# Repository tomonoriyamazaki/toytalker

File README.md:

# ToyTalker

子供向け音声AIおもちゃ。話しかけると、好きなキャラクターの声で返事をしてくれる。

## 特徴

- **応答約2秒**: STT→LLM→TTSを全区間ストリーミングでつなぎ、最初の音声チャンクが生成され次第再生を開始。サーバーレス（AWS Lambda）構成のまま体感レイテンシを最小化
- **相槌**: メインの応答を生成している間に「そうだね〜」などの短い繋ぎ応答を先に返し、会話のテンポを保つ
- **ボイス・キャラクター切替**: TTSプロバイダーをプラガブルに切替可能（OpenAI / Google / Gemini / ElevenLabs / Cartesia / FishAudio / ずんだもん / 自前クローンボイス）。キャラクターの人格プロンプトもDBで管理
- **スタンドアロン動作**: ESP32-S3搭載の専用基板、おもちゃ単体でWiFi経由でAWSと直接通信（設定ではスマホが必要）

## しくみ
https://github.com/user-attachments/assets/177e0598-6c0a-4d14-9477-36d719003d13

```
[スマホアプリ / ESP32] ── 音声 ──> Soniox STT（直接WebSocket接続）
        │                              │ テキスト
        │                              v
        │<── 音声ストリーム ── Lambda（LLM → TTS ストリーミング）
        │<── 繋ぎ応答 ─────── Lambda（相槌）
```

- STTはLambdaを経由せず、一時キーを使ってクライアントからSonioxへ直接接続（ボトルネック回避）
- LLM→TTSは直列ストリーミングで、生成しながら順次音声化・再生

## デバイスの変遷

| 世代 | 構成 | 状態 |
|---|---|---|
| v1 | Raspberry Pi | 検証完了 |
| v2 | ブレッドボード | 検証完了 |
| v3 | ESP32-S3スタンドアロン（専用PCB） | 開発中 |

## 参加プログラム

- SS Bootcamp 3rd #2025
- TiB FAB makers challenge 2025
- SS Bootcamp 4th #2026

## ドキュメント

- [開発のあゆみ（初期からの検討・試行錯誤の記録）](docs/history.md)
- [マイコン（ESP32）実装](docs/mcu.md)
- [スマホアプリ実装](app/README.md)
- [自前クローンボイス（RTX 5090 / Qwen3-TTS）のバッチ推論](docs/qwen3-tts-batch-engine-2026-09-12.md)
- [原価と課金の考え方](docs/pricing-and-cost-model.md)
- [製品化の認証チェックリスト（STマーク・技適・PSE）](docs/certification-checklist.md)

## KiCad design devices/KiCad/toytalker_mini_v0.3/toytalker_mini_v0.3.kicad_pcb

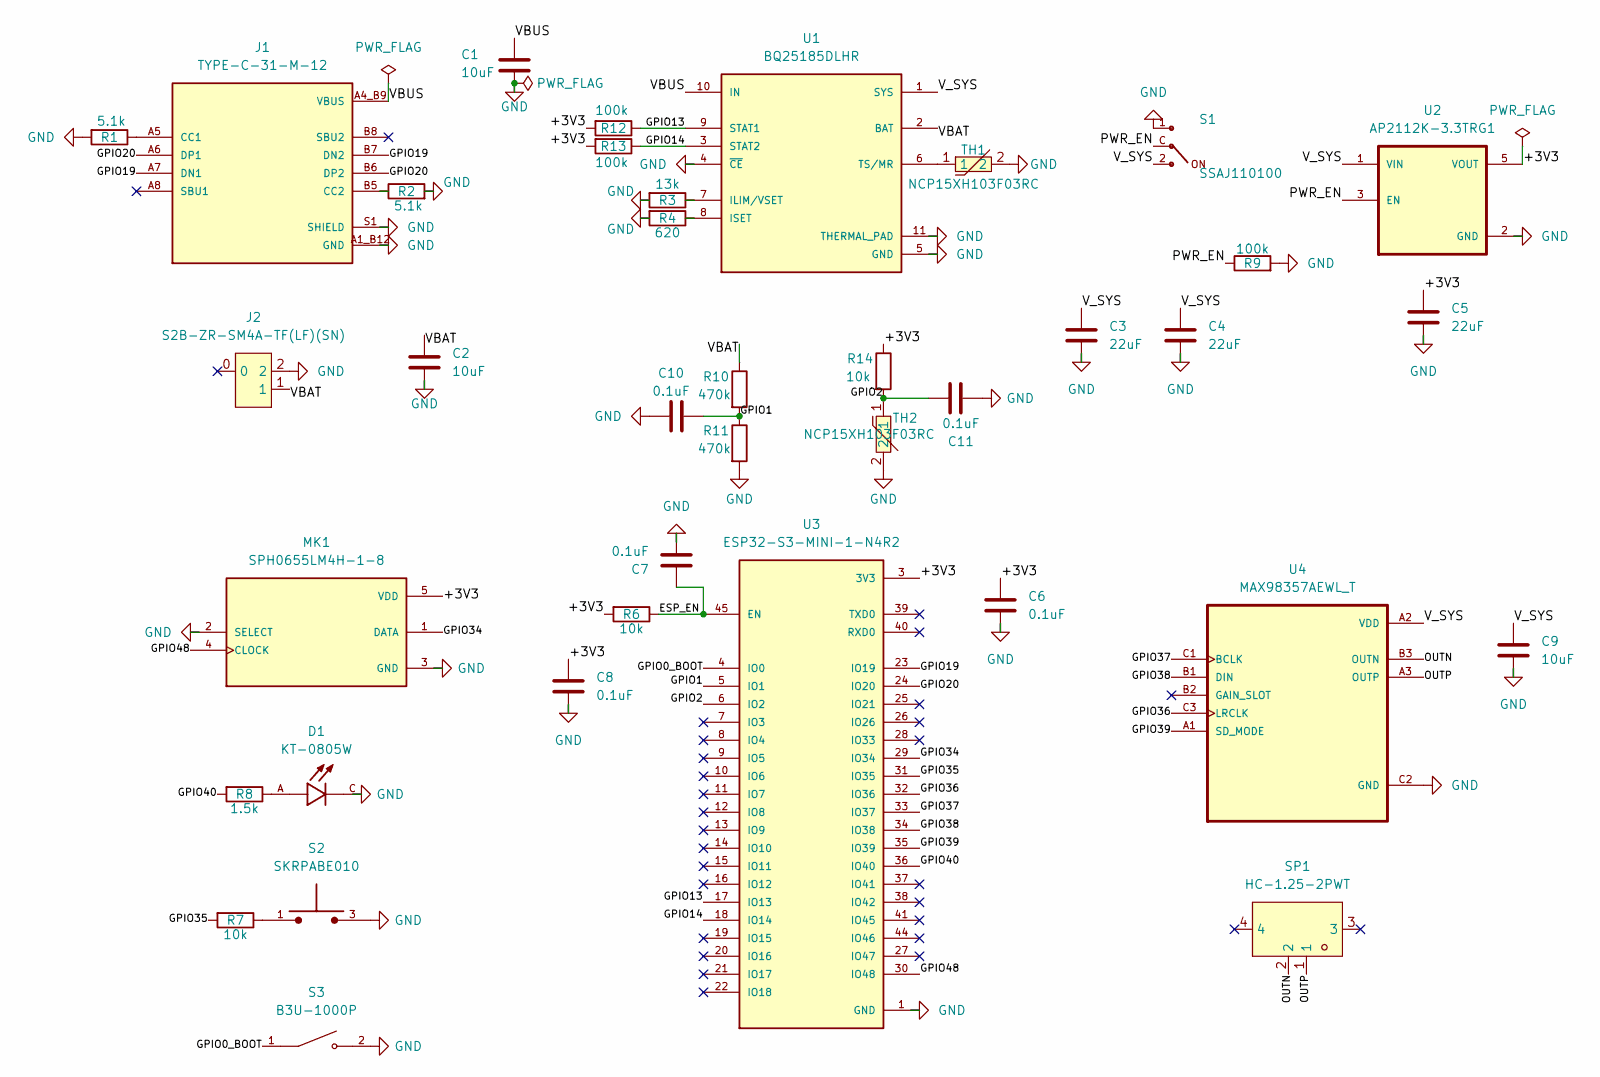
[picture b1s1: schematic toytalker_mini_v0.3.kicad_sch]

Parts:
C1, C2, C9: 10uF; C_0603_1608Metric; LCSC Part C19702
C3, C4, C5: 22uF; C_0603_1608Metric; LCSC Part C59461
C6, C7, C8, C10, C11: 0.1uF; C_0402_1005Metric; LCSC Part C1525
D1: KT-0805W; LED_KT-0805W; PARTREV 2017.05.16; LCSC Part C34499
J1: TYPE-C-31-M-12; HRO_TYPE-C-31-M-12; PARTREV 2020.12.08; LCSC Part C165948
J2: S2B-ZR-SM4A-TF(LF)(SN); CONN-SMD_S2B-ZR-SM4A; LCSC Part C265329
MK1: SPH0655LM4H-1-8; MIC_SPH0655LM4H-1; LCSC Part C22376158
R1, R2: 5.1k; R_0402_1005Metric; LCSC Part C25905
R3: 13k; R_0402_1005Metric; LCSC Part C25754
R4: 620; R_0402_1005Metric; LCSC Part C4961
R6, R7, R14: 10k; R_0402_1005Metric; LCSC Part C25744
R8: 1.5k; R_0402_1005Metric; LCSC Part C25867
R9, R12, R13: 100k; R_0402_1005Metric; LCSC Part C25741
R10, R11: 470k; R_0402_1005Metric; LCSC Part C25790
S1: SSAJ110100; SW_SSAJ110100; LCSC Part C160863
S2: SKRPABE010; SW_SKRPABE010; LCSC Part C115360
S3: B3U-1000P; SW_B3U-1000P; LCSC Part C231329
SP1: HC-1.25-2PWT; CONN-SMD_2P-P1.25-HC-1.25-2PWT; LCSC Part C2845379
TH1, TH2: NCP15XH103F03RC; R0402; LCSC Part C77131
U1: BQ25185DLHR; IC_BQ25185DLHR; PARTREV OCTOBER 2023; LCSC Part C19725033
U2: AP2112K-3.3TRG1; SOT95P285X140-5N; PARTREV 2-2; LCSC Part C23380830
U3: ESP32-S3-MINI-1-N4R2; XCVR_ESP32-S3-MINI-1-N4R2; PARTREV v0.6; LCSC Part C3013941
U4: MAX98357AEWL_T; BGA9N40P3X3_134X143X69N; LCSC Part C2682619

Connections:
/+3V3: C5.1, C6.1, C8.1, MK1.5 (VDD), R6.2, R12.2, R13.2, R14.1, U2.5 (VOUT), U3.3 (3V3)
/ESP_EN: C7.1, R6.1, U3.45 (EN)
/GPIO0_BOOT: S3.1, U3.4 (IO0)
/GPIO1: C10.1, R10.2, R11.1, U3.5 (IO1)
/GPIO2: C11.1, R14.2, TH2.1, U3.6 (IO2)
/GPIO13: R12.1, U1.9 (STAT1), U3.17 (IO13)
/GPIO14: R13.1, U1.3 (STAT2), U3.18 (IO14)
/GPIO19: J1.A7 (DN1), J1.B7 (DN2), U3.23 (IO19)
/GPIO20: J1.A6 (DP1), J1.B6 (DP2), U3.24 (IO20)
/GPIO34: MK1.1 (DATA), U3.29 (IO34)
/GPIO35: R7.2, U3.31 (IO35)
/GPIO36: U3.32 (IO36), U4.C3 (LRCLK)
/GPIO37: U3.33 (IO37), U4.C1 (BCLK)
/GPIO38: U3.34 (IO38), U4.B1 (DIN)
/GPIO39: U3.35 (IO39), U4.A1 (SD_MODE)
/GPIO40: R8.2, U3.36 (IO40)
/GPIO48: MK1.4 (CLOCK), U3.30 (IO48)
/OUTN: SP1.2, U4.B3 (OUTN)
/OUTP: SP1.1, U4.A3 (OUTP)
/PWR_EN: R9.1, S1.C, U2.3 (EN)
/VBAT: C2.1, J2.1, R10.1, U1.2 (BAT)
/V_SYS: C3.1, C4.1, C9.1, S1.2, U1.1 (SYS), U2.1 (VIN), U4.A2 (VDD)
GND: C1.2, C2.2, C3.2, C4.2, C5.2, C6.2, C7.2, C8.2, C9.2, C10.2, C11.2, D1.C, J1.A1_B12 (GND), J1.B1_A12 (GND), J1.S1 (SHIELD), J1.S2 (SHIELD), J1.S3 (SHIELD), J1.S4 (SHIELD), J2.2, MK1.2 (SELECT), MK1.3 (GND), R1.2, R2.2, R3.2, R4.2, R9.2, R11.2, S1.1, S2.3, S2.4, S3.2, TH1.2, TH2.2, U1.4 (~CE), U1.5 (GND), U1.11 (THERMAL_PAD), U1.12, U1.13, U2.2 (GND), U3.1 (GND), U3.2 (GND), U3.42 (GND), U3.43 (GND), U3.46 (GND), U3.47 (GND), U3.48 (GND), U3.49 (GND), U3.50 (GND), U3.51 (GND), U3.52 (GND), U3.53 (GND), U3.54 (GND), U3.55 (GND), U3.56 (GND), U3.57 (GND), U3.58 (GND), U3.59 (GND), U3.60 (GND), U3.61 (GND), U3.61_1 (GND), U3.61_2 (GND), U3.61_3 (GND), U3.61_4 (GND), U3.61_5 (GND), U3.61_6 (GND), U3.61_7 (GND), U3.61_8 (GND), U3.62 (GND), U3.63 (GND), U3.64 (GND), U3.65 (GND), U4.C2 (GND)
unnamed: D1.A, R8.1
unnamed: J1.A5 (CC1), R1.1
unnamed: J1.B5 (CC2), R2.1
unnamed: R7.1, S2.1, S2.2
unnamed: R3.1, U1.7 (ILIM/VSET)
unnamed: R4.1, U1.8 (ISET)
unnamed: TH1.1, U1.6 (TS/MR)
VBUS: C1.1, J1.A4_B9 (VBUS), J1.B4_A9 (VBUS), U1.10 (IN)

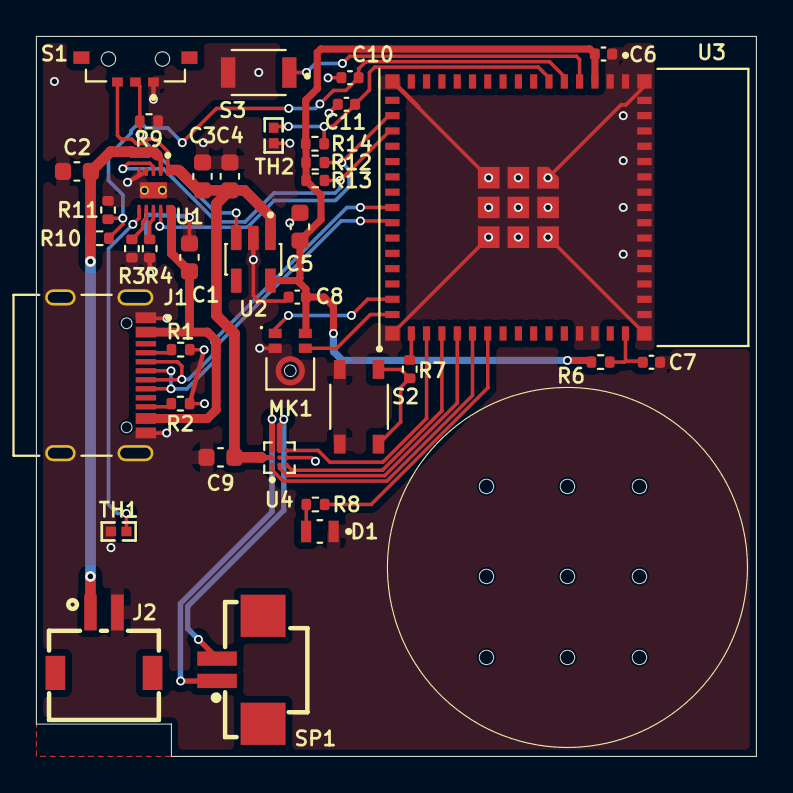
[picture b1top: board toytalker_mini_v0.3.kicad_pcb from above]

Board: 2 copper layers, 40.0 x 40.0 mm, 38 parts (0 on the bottom side), 31 nets.

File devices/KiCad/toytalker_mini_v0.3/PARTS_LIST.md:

# v0.3 パーツ一覧（v0.2 の実値を引き継ぎ、3点だけ変更。2026-11-08）

> **このファイルの役割: 「今の正」。** 部品の値・ネット・役割の唯一の基準。BOM作成・発注チェック・値の確認はこのファイルだけを見る。変更したら必ずここを更新する。
> 経緯・理由 → [v0.2 の PARTS_AND_POWER.md](../toytalker_mini_v0.2/PARTS_AND_POWER.md)（v0.3 の候補選定「v0.3 マイク代替検討」もここ）/ GPIO → PINMAP.md / 配置の地図 → [v0.2 の LAYOUT_PLAN.md](../toytalker_mini_v0.2/LAYOUT_PLAN.md)（v0.3 は配置を動かしていない）

検証方法: `toytalker_mini_v0.3.kicad_sch` から全Reference/Valueを抽出し、ネットリストで接続先を照合。ERC 0件。DRC は v0.2 と同じ既知の指摘だけ（下記「設計の状態」）。

## v0.2 からの変更点（3つ）

| Ref | v0.2 | v0.3 | 理由・注意 |
|---|---|---|---|
| **MK1** | SPH0645LM4H-1-8（I2S、6パッド、生産終了） | **SPH0655LM4H-1-8**（Knowles Cornell II、**PDM**、5パッド、LCSC C22376158） | 0645 は DigiKey で Obsolete。ランドパターンが違う（列間 1.675 / 行間 0.822 / ポート中心から下段パッド中心まで 1.252（データシートの 1.513 はパッドの縁まで）、パッド 0.725×0.522、GNDリング Ø1.025/1.625）ので Knowles データシート Rev C から新フットプリント `MIC_SPH0655LM4H-1` を起こし、JLCPCB（EasyEDA）の C22376158 のフットプリントとパッド位置・寸法が一致することを確認済み（EasyEDA 側は GND リングが幅 0.07mm の線になっていて使えない）。ポート穴は **Ø0.65**（v0.2 の 0.5 から変更。データシート推奨 0.6〜1.0、EasyEDA と同じ）、I2S の WS 線（GPIO33）が不要になり未接続に。**ファームは PDM 受信に書き換えが要る**（PINMAP.md）。2軍の Goertek SD18OB261-060（C2895290）はピン・ランドパターンとも同一で BOM 差し替えだけで載る |
| **R8** | 470Ω（約1.1mA） | **1.5kΩ**（約0.33mA、1/3） | LED をさらに暗く。KT-0805W の順方向電圧は 2.6〜3.0V @2mA（Kento データシート）なので 3.3V 駆動では (3.3−2.8)/R。v0.2 の「約2.8mA」は Vf=2V の仮定で、実際は約1.1mA（0.6〜1.5mA）だった。1.5kΩ で 0.2〜0.47mA（Vf のばらつき分）。もっと暗くするなら 2.2kΩ（約0.23mA）。細かい調整はファームの PWM（`ledc`）でもできる |
| **S1** | MSK12C02G15-B（ノブ 1.5mm、本体高 1.45mm） | **ALPS SSAJ110100**（v0.1 で使った品。本体高 0.7mm、ノブ 1.3mm、LCSC C160863） | v0.1 のフットプリント `SW_SSAJ110100` を流用（ノブ側のシルクだけ消した）。基板上辺（y=12）に本体の端をぴったり合わせ、ノブは 1.3mm 外へ出る。配線は EN 方式のまま: **C=PWR_EN、2=V_SYS、1=GND**（v0.1 と同じ C–2 で ON）。**ケース側の掛かり代は要再設計**（ノブの高さが 1.45→0.7mm、突き出しが 0.5→1.3mm） |

## パーツ一覧 ※電気の流れ順

### USB受電 → 充電IC
| Ref | 値 | ネット | 役割 |
|---|---|---|---|
| J1 | TYPE-C-31-M-12 | VBUS | USB-C電源入力 |
| R1 | 5.1kΩ | CC1 | USB-C「5V/3Aください」の名札(必須) |
| R2 | 5.1kΩ | CC2 | 同上(ケーブル裏表対応) |
| C1 | 10uF | VBUS | BQ25185のIN入力デカップリング |
| U1 | BQ25185 | - | 電源制御。充電しながら電力供給(パワーパス) |
| R3 | 13kΩ | ILIM/VSET | USBから最大1.1A受電の設定 |
| R4 | **620Ω** | ISET | バッテリーへ500mA充電の設定 |
| TH1 | NCP15XH103F03RC | TS/MR | 充電温度保護サーミスタ。高温/低温でBQが充電を自動停止 |

### バッテリー
| Ref | 値 | ネット | 役割 |
|---|---|---|---|
| J2 | S2B-ZR-SM4A-TF | VBAT | バッテリーコネクタ(JST ZH、φ1.0被覆線対応) |
| C2 | 10uF | VBAT | BQ25185のBAT側デカップリング |

### システム電源 V_SYS（常時通電）
| Ref | 値 | ネット | 役割 |
|---|---|---|---|
| C3 | 22uF | V_SYS | BQ25185のSYS出力デカップリング |
| C4 | 22uF | V_SYS | 同上追加分 |

### 電源スイッチ（EN方式 = 信号だけを切り替える）
| Ref | 値 | ネット | 役割 |
|---|---|---|---|
| S1 | **SSAJ110100** | PWR_EN | 🔁 スライドスイッチ（ALPS、横操作、SPDT）。C→PWR_EN、2→V_SYS、1→GND。C–2 が閉じると ON（大電流は流れない） |
| R9 | 100kΩ | PWR_EN | プルダウン。スイッチ切替中にENが宙ぶらりんになるのを防ぐ「重り」 |

### LDO → +3V3
| Ref | 値 | ネット | 役割 |
|---|---|---|---|
| U2 | AP2112K-3.3 | - | LDO。V_SYS→3.3Vに降圧。ENピンがPWR_ENで電源ON/OFF |
| C5 | 22uF | +3V3 | LDO出力デカップリング |
| C6 | 0.1uF | +3V3 | ESP32直近の高周波デカップリング |
| C8 | 0.1uF | +3V3 | マイク直近デカップリング |

### ESP32まわり
| Ref | 値 | ネット | 役割 |
|---|---|---|---|
| U3 | ESP32-S3-MINI-1-N4R2 | - | 本体（実寸15.4×20.5mm、アンテナ部5.05mm含む） |
| R6 | 10kΩ | ESP_EN | ENプルアップ |
| C7 | 0.1uF | ESP_EN | ENの立ち上がり遅延+ノイズフィルタ |
| S3 | B3U-1000P | GPIO0_BOOT | Bootボタン |
| S2 | SKRPABE010 | GPIO35 | 機能ボタン(押すとGND) |
| R7 | 10kΩ | GPIO35 | ボタンとGPIOの間の直列抵抗(ピン保護) ※プルダウンではない |
| D1 | KT-0805W | GPIO40 | 単色LED（白、Vf 2.6〜3.0V @2mA、IF max 20mA） |
| R8 | **1.5kΩ** | GPIO40 | 🔁 LED電流制限。v0.3 で 470Ω→1.5kΩ（約0.33mA、v0.2 の 1/3） |

### 監視・計測
| Ref | 値 | ネット | 役割 |
|---|---|---|---|
| R10 | 470kΩ | VBAT→GPIO1 | 電池残量分圧の上側 |
| R11 | 470kΩ | GPIO1→GND | 電池残量分圧の下側 |
| C10 | 0.1uF | GPIO1 | ADC安定化(WiFiノイズ平滑) |
| R12 | 100kΩ | GPIO13 | 充電状態STAT1プルアップ(STATはオープンドレインのため必須) |
| R13 | 100kΩ | GPIO14 | 充電状態STAT2プルアップ |
| R14 | 10kΩ | +3V3→GPIO2 | 基板温度分圧の上側 |
| TH2 | NCP15XH103F03RC | GPIO2→GND | 基板温度サーミスタ(分圧の下側) |
| C11 | 0.1uF | GPIO2 | ADC安定化 |

### 音声
| Ref | 値 | ネット | 役割 |
|---|---|---|---|
| MK1 | **SPH0655LM4H-1-8** | GPIO48(CLOCK)/GPIO34(DATA) | 🔁 **PDM** マイク。1=DATA→GPIO34、2=SELECT→GND、3=GND(リング)、4=CLOCK→GPIO48、5=VDD→+3V3。感度 -37dBFS（0645 は -26。ファームで約 +11dB）、SNR 66dB(A)、AOP 132.5dB SPL |
| U4 | MAX98357A | - | I2Sアンプ。VDDは**V_SYS直結**(3.3Vでは音量パワー不足のため) |
| C9 | 10uF | **V_SYS** | アンプVDDデカップリング ※+3V3ではない |
| SP1 | HC-1.25-2PWT | OUTP/OUTN | スピーカーコネクタ(MX1.25互換) |

## プレフィックス順サマリ
- **J**: J1 USB-C / J2 バッテリー(ZH)
- **U**: U1 BQ25185 / U2 AP2112K / U3 ESP32-S3-MINI-1 / U4 MAX98357A
- **S**: S1 電源スライド(SSAJ110100) / S2 機能 / S3 Boot
- **R**: R1,R2=5.1k(CC) R3=13k(ILIM) R4=620(ISET) R6=10k(EN) R7=10k(ボタン直列) **R8=1.5k(LED)** R9=100k(PWR_ENプルダウン) R10,R11=470k(残量分圧) R12,R13=100k(STATプルアップ) R14=10k(温度分圧)
- **C**: C1,C2=10u(VBUS/VBAT) C3,C4=22u(V_SYS) C5=22u,C6=0.1u,C8=0.1u(+3V3) C7=0.1u(EN) C9=10u(V_SYS アンプ) C10,C11=0.1u(ADC)
- **TH**: TH1 充電保護 / TH2 基板温度 (同一品NCP15XH103F03RC)
- **他**: D1 LED / MK1 マイク(PDM) / SP1 スピーカー

## パッケージサイズの使い分け

サイズ表記: **0402** = 1.0×0.5mm / **0603** = 1.6×0.8mm（インチ由来の呼び名。メートル表記だと1005/1608でKiCadのフットプリント名はこちら）

| 種類 | サイズ | 理由 |
|---|---|---|
| 抵抗 全部(R1〜R14, TH1/TH2) | **0402** | 抵抗のサイズは**発熱**で決まり、値は無関係。R8 は 1.5kΩ 化で 0.2mW 未満 |
| コンデンサ 0.1µF (C6/C7/C8) | **0402** | 小容量は小さい体積で作れる |
| コンデンサ 10〜22µF (C1〜C5, C9) | **0603** | 容量は物理体積が必要。0402の10µFは高価な上、電圧がかかると実効容量が大きく落ちる(DCバイアス特性)ため0603が定石 |

※C10/C11(0.1µF)は v0.2 と同じく 0603 のまま（0402 への統一は未実施）。

## 設計の状態（2026-11-08）

- **何を変えたか（基板）**: U1（BQ25185）の放熱パッド下のビア 2 個を穴 0.2/ランド 0.4 → **穴 0.3/ランド 0.5** に（JLCPCB の「穴 0.3mm 未満かつビア径 0.4 以下は追加料金」を避ける。基板上の穴は 0.3 以上だけに）。MK1 のフットプリント差し替え（原点は v0.2 と同じ (26.1, 30.574)。DATA・CLOCK・+3V3 の配線の先端だけ新パッドへ付け替え、SELECT は裏面ベタGNDへのビア 1 個で落とす。GPIO33 の配線・ビア 2 個は削除）。S1 を `SW_SSAJ110100` に差し替え（原点 (17.5, 13.25)、180°。V_SYS / PWR_EN / GND の 3 本を新パッドへ付け替え）。R8 の値。ほかの部品と配線は v0.2 のまま。
- **ERC**: 0件。**DRC**（ゾーン再充填後、回路図との照合つき）: 20件で、内訳は v0.2 と同じ既知のもの（U4 BGA のマスク橋渡し 11、J1 シールドの基板端 0.48mm 2、J1 シルク 2、U1/U3 のライブラリ不一致 2、U1 放熱穴のネット未定義 2、S2/U3 シルク重なり 1）＋ MK1 の音孔まわりのマスク開口が NPTH と重なる注意 1（v0.2 と同じ描き方で、意図どおり）。未接続パッド 0。スピーカー音抜き穴（参照名なしの 9 個）は「回路図に無い」と出るが v0.2 からある。
- **発注前に必ず**（[マイコン](../../../docs/mcu.md) の「発注前チェック」）: KiCad で開いて 3D ビューア（MK1 と S1 は 3D モデル未割当。v0.2 も同じ）、**原寸紙テスト（SSAJ の実物をノブの出代 1.3mm で確認）**、JLCPCB の DFM。製造ファイルは `production/` に出力済み（2026-11-08、Fabrication Toolkit を CLI で実行。bom.csv は v0.2 と MK1・R8・S1 の 3 行だけ違い、positions.csv は S1 の位置と角度だけ違う。ガーバーの zip は git に入らないので、発注前に [マイコン](../../../docs/mcu.md) のコマンドで出し直す）。JLCPCB へは zip・bom.csv・positions.csv の 3 つを上げる。**全部品の LCSC 番号を回路図と基板の `LCSC Part` 項目に入れた**（v0.2 の注文で実際に選んだ番号。R8 の 1.5kΩ だけ新規に Basic の 0402WGF1501TCE = C25867）ので、bom.csv は全行に番号が入り、JLCPCB 側で部品を選び直す作業は不要。部品を変えたら `LCSC Part` も直す。
- **ケース**: スイッチの高さと出代が変わる（上記）。
- **ファーム**: PDM 化が必要（PINMAP.md）。v0.3 基板に v0.7 ファームをそのまま入れても録音できない。
- **このフォルダに無いもの**: `resources/`（部品の元データ）と v0.2 の発注出力 `production/`・原寸 PDF・設計の経過文書は v0.2 フォルダに残してある。
